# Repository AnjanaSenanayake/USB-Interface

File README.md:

# General Purpose Input Output Board Using USB-Interface

Communication via USB is the most popular mode of interfacing nowadays. Almost all the peripherals that have other kind of interfacing (serial port, parallel port..) are converting the ports to be compatible with USB. Building a general USB interface that can later be extended to industrial components handling is of major concern. Because of this reason leaders in microcontroller designing have explicitly designed microchips that can support USB protocol. This attempt is to program one such microchip to build a general I/O board. The board will be hereafter referred as the GIOB. GIOB has the following features. 

- can read 16 input lines 
- can write to 8 output lines 
- no external power supply required, power is supplied via the PC’s USB bus 
- compatible with USB 2.0, 3.0

To design GIOB we use the PIC18F4550 USB module which is a 8 bit PIC microcontroller. We chose this module as it has a stable clock for full-speed USB operation and is widely used for USB communication. Also the designer of this microcontroller, MICROCHIP has provided the tools to program the IC. Since this IC is the widely used component in this field there is an active supportive community. 

To start with the project, we are going to refer ​USB interface to the PIC Microcontroller  Then, extend the design and the concept to more generalized plug and play I/O interface with maximum data lines possible.

More infomation can be found in the documentation.

### Original sources
1. https://www.youtube.com/watch?v=WO99avWTujs
2. https://github.com/MicrocontrollersAndMore/Updated_PIC_18F4550_USB_Demo_Board

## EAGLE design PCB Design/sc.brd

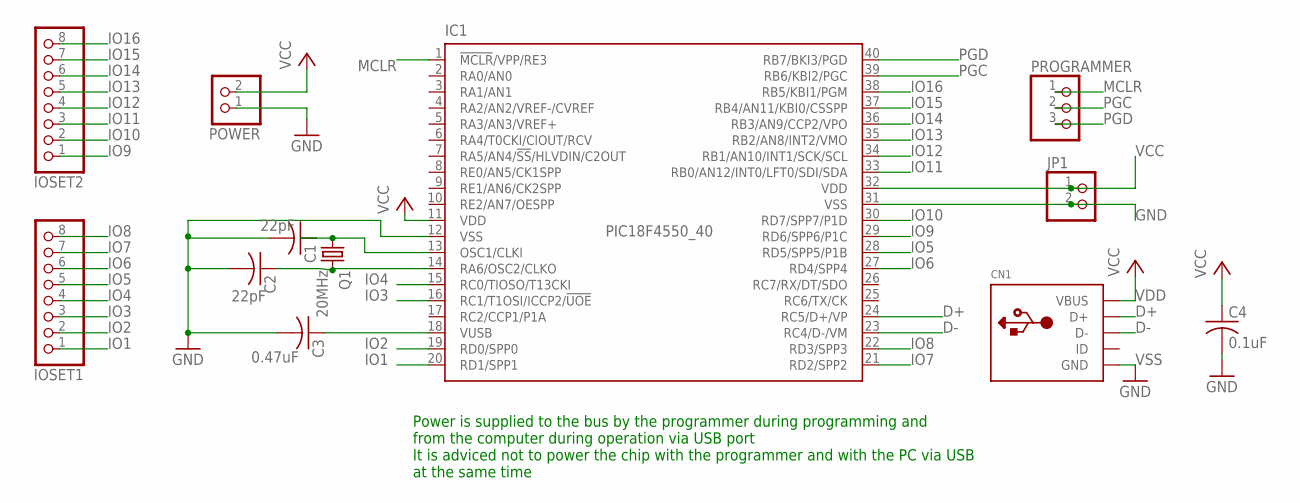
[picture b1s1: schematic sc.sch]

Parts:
C1, C2: 22pF; C025-024X044
C3: 0.47uF; C025-024X044
C4: 0.1uF; C025-024X044
CN1: USBTHM; USB-MINIB-THM
IC1: PIC18F4550_40; DIL40
IOSET1, IOSET2: PINHD-1X8; 1X08
JP1: PINHD-1X2; 1X02
POWER: PINHD-1X2; 1X02
PROGRAMMER: PINHD-1X3; 1X03
Q1: 20MHz; HC18U-V

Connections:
D+: CN1.D+, IC1.24 (RC5/D+/VP)
D-: CN1.D-, IC1.23 (RC4/D-/VM)
GND: C1.2, C2.2, C3.2, C4.2, IC1.12 (VSS), IC1.31 (VSS), JP1.2, POWER.1
IO1: IC1.20 (RD1/SPP1), IOSET1.1
IO2: IC1.19 (RD0/SPP0), IOSET1.2
IO3: IC1.16 (RC1/T1OSI/ICCP2/!UOE), IOSET1.3
IO4: IC1.15 (RC0/TIOSO/T13CKI), IOSET1.4
IO5: IC1.28 (RD5/SPP5/P1B), IOSET1.5
IO6: IC1.27 (RD4/SPP4), IOSET1.6
IO7: IC1.21 (RD2/SPP2), IOSET1.7
IO8: IC1.22 (RD3/SPP3), IOSET1.8
IO9: IC1.29 (RD6/SPP6/P1C), IOSET2.1
IO10: IC1.30 (RD7/SPP7/P1D), IOSET2.2
IO11: IC1.33 (RB0/AN12/INT0/LFT0/SDI/SDA), IOSET2.3
IO12: IC1.34 (RB1/AN10/INT1/SCK/SCL), IOSET2.4
IO13: IC1.35 (RB2/AN8/INT2/VMO), IOSET2.5
IO14: IC1.36 (RB3/AN9/CCP2/VPO), IOSET2.6
IO15: IC1.37 (RB4/AN11/KBI0/CSSPP), IOSET2.7
IO16: IC1.38 (RB5/KBI1/PGM), IOSET2.8
MCLR: IC1.1 (!MCLR!/VPP/RE3), PROGRAMMER.1
unnamed: C1.1, IC1.13 (OSC1/CLKI), Q1.1
unnamed: C2.1, IC1.14 (RA6/OSC2/CLKO), Q1.2
unnamed: C3.1, IC1.18 (VUSB)
PGC: IC1.39 (RB6/KBI2/PGC), PROGRAMMER.2
PGD: IC1.40 (RB7/BKI3/PGD), PROGRAMMER.3
VCC: C4.1, IC1.11 (VDD), IC1.32 (VDD), JP1.1, POWER.2
VDD: CN1.VBUS
VSS: CN1.GND

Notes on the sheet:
Power is supplied to the bus by the programmer during programming and from the computer during operation via USB port It is adviced not to power the chip with the programmer and with the PC via USB at the same time

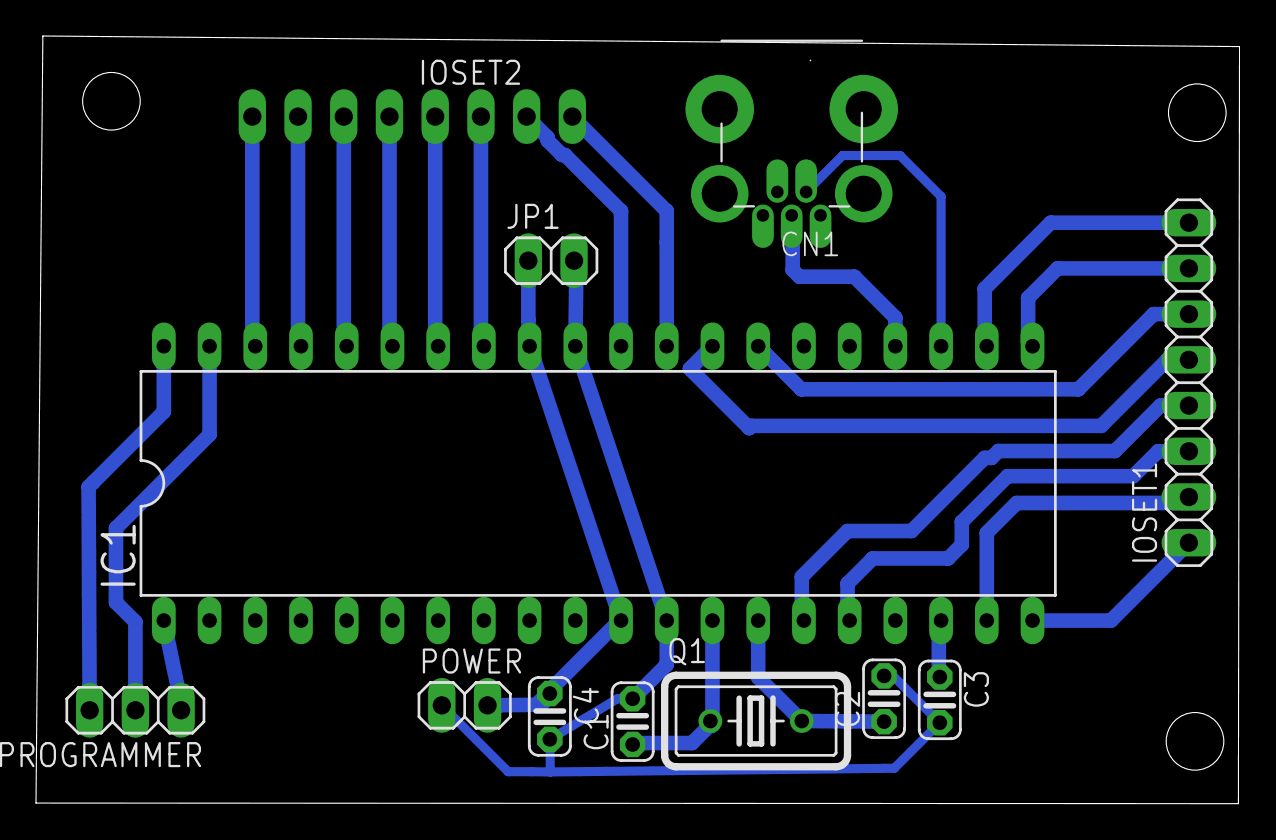
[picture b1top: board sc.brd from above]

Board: 2 copper layers, 66.9 x 42.6 mm, 12 parts (1 on the bottom side), 26 nets.

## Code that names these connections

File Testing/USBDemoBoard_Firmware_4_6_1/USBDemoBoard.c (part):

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#pragma config VREGEN = ON				// USB voltage regulator enabled (If using USB, capacitor goes on pin 18 (VUSB))
#pragma config WDT = OFF				// watchdog timer disabled
#pragma config WDTPS = 32768			// watchdog timer postscale, does not matter since watchdog timer is disabled
#pragma config CCP2MX = ON				// use RC1 (pin #16) as CCP2 MUX (this is the default pin for CCP2 MUX)
#pragma config PBADEN = OFF				// RB0, RB1, RB2, RB3, & RB4 are configured as digital I/O on reset
#pragma config LPT1OSC = OFF			// disable low-power option for timer 1 (timer 1 in regular mode)
#pragma config MCLRE = OFF				// master clear disabled, pin #1 is for VPP and / or RE3 use
#pragma config STVREN = ON				// stack full/underflow will cause reset
#pragma config LVP = OFF				// single-supply ICSP disabled
#pragma config ICPRT = OFF				// in-circuit debug/programming port (ICPORT) disabled, this feature is not available on 40 pin DIP package
#pragma config XINST = OFF				// instruction set extension and indexed addressing mode disabled (this is the default setting)
#pragma config DEBUG = OFF				// background debugger disabled, RA6 & RB7 configured as general purpose I/O pins
#pragma config CP0 = OFF, CP1 = OFF, CP2 = OFF, CP3 = OFF			// code protection bits off
#pragma config CPB = OFF				// boot block code protection off
#pragma config CPD = OFF				// data EEPROM code protection off
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#define REMAPPED_LOW_INTERRUPT_VECTOR_ADDRESS	0x1018			// do not change these !!


#define SWITCH1		PORTDbits.RD1			// input pins
#define SWITCH2		PORTDbits.RD2
// $1
#define SWITCH0		PORTDbits.RD0   //portd
#define SWITCH3		PORTDbits.RD3
#define SWITCH4		PORTDbits.RD4
#define SWITCH5		PORTDbits.RD5
#define SWITCH6		PORTDbits.RD6
#define SWITCH7		PORTDbits.RD7


#define LED1	PORTBbits.RB1			// output pins
#define LED2	PORTBbits.RB2
#define LED3	PORTBbits.RB3
// @1
#define LED4	PORTBbits.RB4			//#2
#define LED0	PORTBbits.RB0			//#2
#define LED5	PORTBbits.RB5			//#2
#define LED6	PORTCbits.RC0			//#2
#define LED7	PORTCbits.RC1			//#2


#define LED1_ON		0x01			// LED command states
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	ADCON1bits.PCFG1 = 1;			//
	ADCON1bits.PCFG0 = 1;			//
									
	TRISDbits.RD1 = 1;				// config input pins
	TRISDbits.RD2 = 1;
// $3
	TRISDbits.RD0 = 1; //portD
	TRISDbits.RD3 = 1;
	TRISDbits.RD4 = 1;
	TRISDbits.RD5 = 1;
	TRISDbits.RD6 = 1;
	TRISDbits.RD7 = 1;


	TRISBbits.TRISB3 = 0;			// set RB3 to output
	TRISBbits.TRISB2 = 0;			// set RB2 to output
	TRISBbits.TRISB1 = 0;			// set RB1 to output
	// @3
	TRISBbits.TRISB4 = 0;			// set RB4 to output 	#@
	TRISBbits.TRISB0 = 0;			// set RB0 to output 	#@
	TRISBbits.TRISB5 = 0;			// set RB5 to output 	#@
	TRISCbits.TRISC0 = 0;			// set RC0 to output 	#@
	TRISCbits.TRISC1 = 0;			// set RC1 to output 	#@

	LED3 = 0;						// init output pins to off
	LED2 = 0;
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
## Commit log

2019-01-04 Initial
2020-05-19 final files with documentation
2020-05-21 Adding PCB files
2020-05-21 update original sources
